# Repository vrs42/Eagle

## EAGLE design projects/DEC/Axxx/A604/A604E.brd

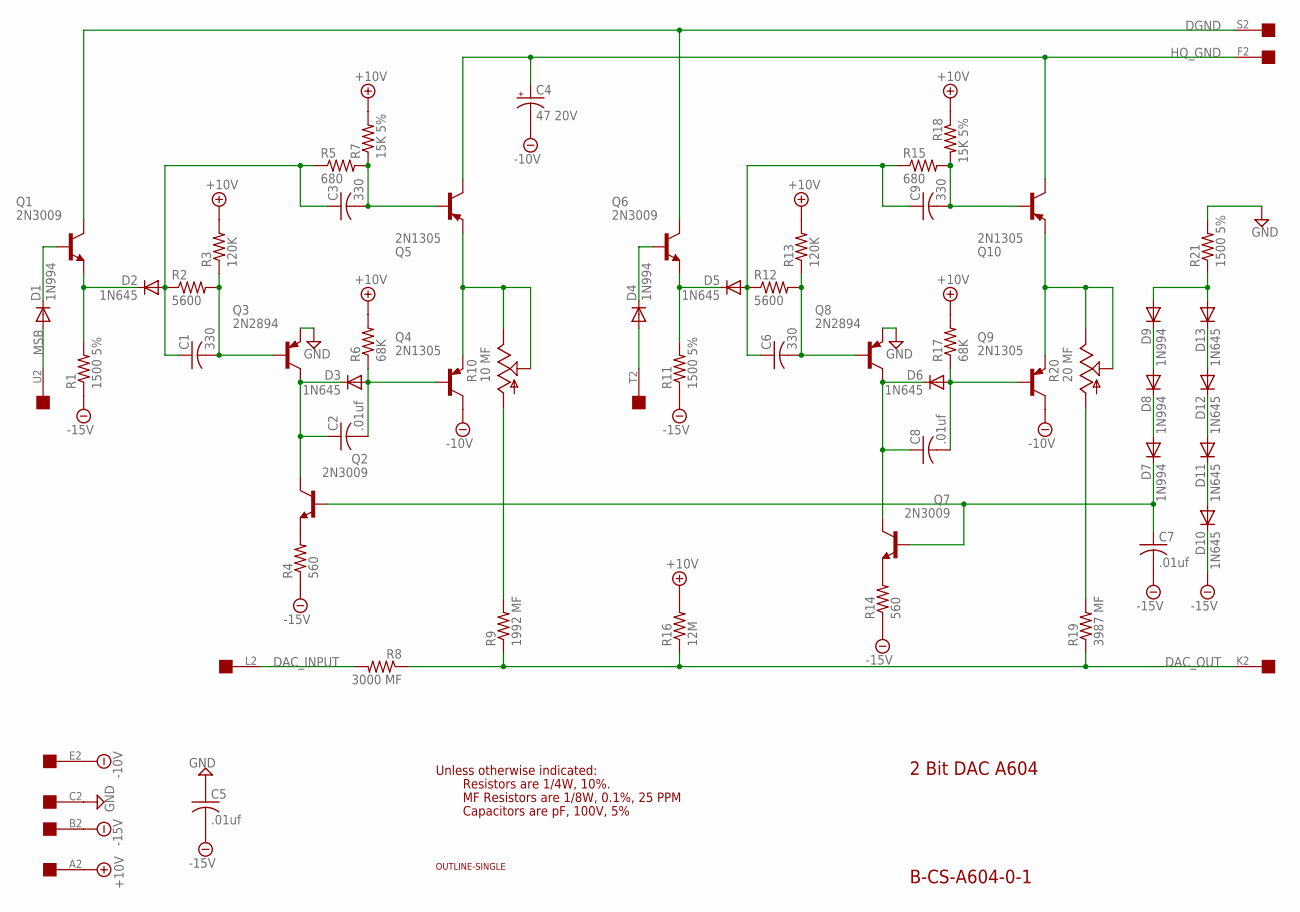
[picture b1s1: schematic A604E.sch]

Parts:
C1, C3, C6, C9: 330; C075-032X103
C2, C5, C7, C8: .01uf; C050-025X075
C4: 47 20V; E22-6
D1, D4, D7, D8, D9: 1N994; DO35-10
D2, D3, D5, D6, D10, D11, D12, D13: 1N645; DO35-10
Q1, Q2, Q6, Q7: 2N3009; TO39
Q3, Q8: 2N2894; TO39
Q4, Q5, Q9, Q10: 2N1305; TO39
R1, R11, R21: 1500 5%; 0207/10
R2, R12: 5600; 0207/10
R3, R13: 120K; 0207/10
R4, R14: 560; 0207/10
R5, R15: 680; 0207/10
R6, R17: 68K; 0207/10
R7, R18: 15K 5%; 0207/10
R8: 3000 MF; 0309/12
R9: 1992 MF; 0309/12
R10: 10 MF; S75P
R16: 12M; 0207/10
R19: 3987 MF; 0309/12
R20: 20 MF; S75P
U$1: OUTLINE-SINGLE; SINGLE
U$3: EDGE-1; EDGE-CON1

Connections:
+10V: R3.2, R6.2, R7.2, R13.2, R16.2, R17.2, R18.1, U$3.A2
-10V: C4.-, Q4.3 (C), Q9.3 (C), U$3.E2
-15V: C5.2, C7.2, D10.C, R1.1, R4.1, R11.1, R14.1, U$3.B2
DAC_INPUT: R8.2, U$3.L2
DAC_OUT: R8.1, R9.1, R16.1, R19.1, U$3.K2
DGND: Q1.3 (C), Q6.3 (C), U$3.S2
GND: C5.1, Q3.1 (E), Q8.1 (E), R21.2, U$3.C2
HQ_GND: C4.+, Q5.3 (C), Q10.3 (C), U$3.F2
MSB: D1.A, U$3.U2
unnamed: D1.C, Q1.2 (B)
unnamed: D2.C, Q1.1 (E), R1.2
unnamed: C1.1, C3.1, D2.A, R2.1, R5.1
unnamed: C1.2, Q3.2 (B), R2.2, R3.1
unnamed: C3.2, Q5.2 (B), R5.2, R7.1
unnamed: C2.1, D3.C, Q2.3 (C), Q3.3 (C)
unnamed: C2.2, D3.A, Q4.2 (B), R6.1
unnamed: Q4.1 (E), Q5.1 (E), R10.E, R10.S
unnamed: D4.C, Q6.2 (B)
unnamed: D5.C, Q6.1 (E), R11.2
unnamed: C6.1, C9.1, D5.A, R12.1, R15.1
unnamed: C6.2, Q8.2 (B), R12.2, R13.1
unnamed: C9.2, Q10.2 (B), R15.2, R18.2
unnamed: C8.1, D6.C, Q7.3 (C), Q8.3 (C)
unnamed: C8.2, D6.A, Q9.2 (B), R17.1
unnamed: Q9.1 (E), Q10.1 (E), R20.E, R20.S
unnamed: Q2.1 (E), R4.2
unnamed: R9.2, R10.A
unnamed: R19.2, R20.A
unnamed: Q7.1 (E), R14.2
unnamed: C7.1, D7.C, Q2.2 (B), Q7.2 (B)
unnamed: D8.A, D9.C
unnamed: D7.A, D8.C
unnamed: D10.A, D11.C
unnamed: D12.A, D13.C
unnamed: D11.A, D12.C
unnamed: D9.A, D13.A, R21.1
T2: D4.A, U$3.T2

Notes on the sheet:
2 Bit DAC A604
B-CS-A604-0-1
Unless otherwise indicated:
Resistors are 1/4W, 10%.
MF Resistors are 1/8W, 0.1%, 25 PPM
Capacitors are pF, 100V, 5%

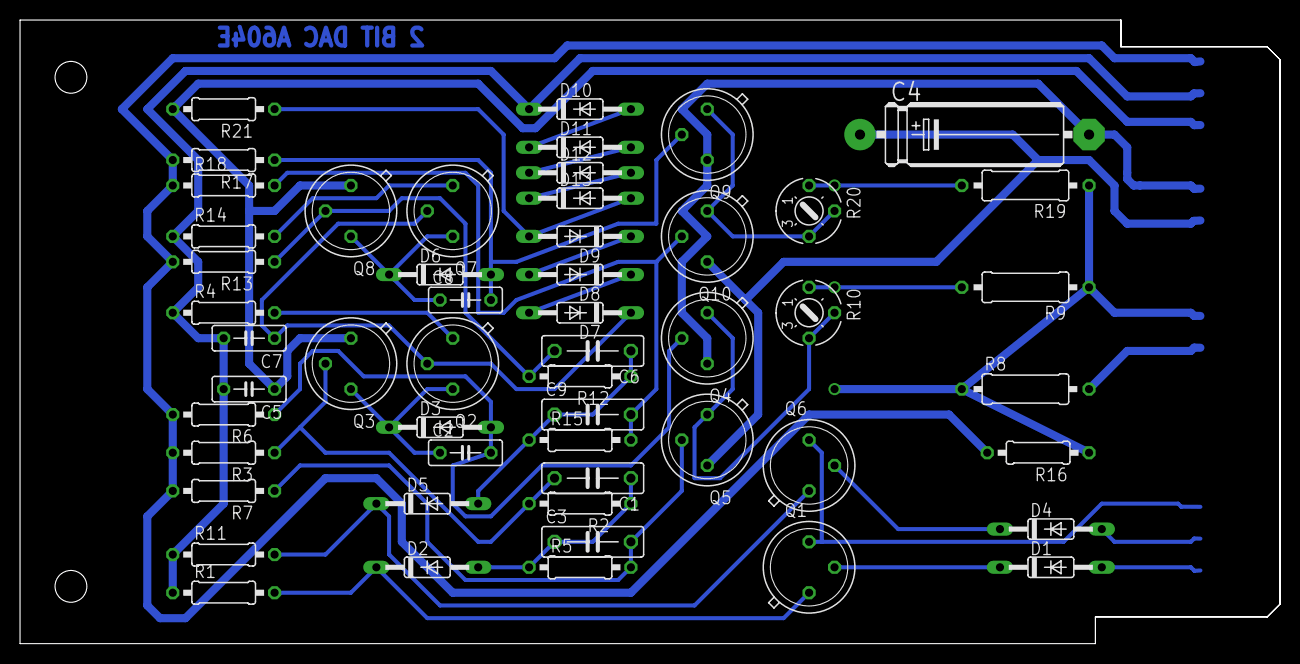
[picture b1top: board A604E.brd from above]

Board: 2 copper layers, 125.7 x 62.2 mm, 55 parts (0 on the bottom side), 37 nets.

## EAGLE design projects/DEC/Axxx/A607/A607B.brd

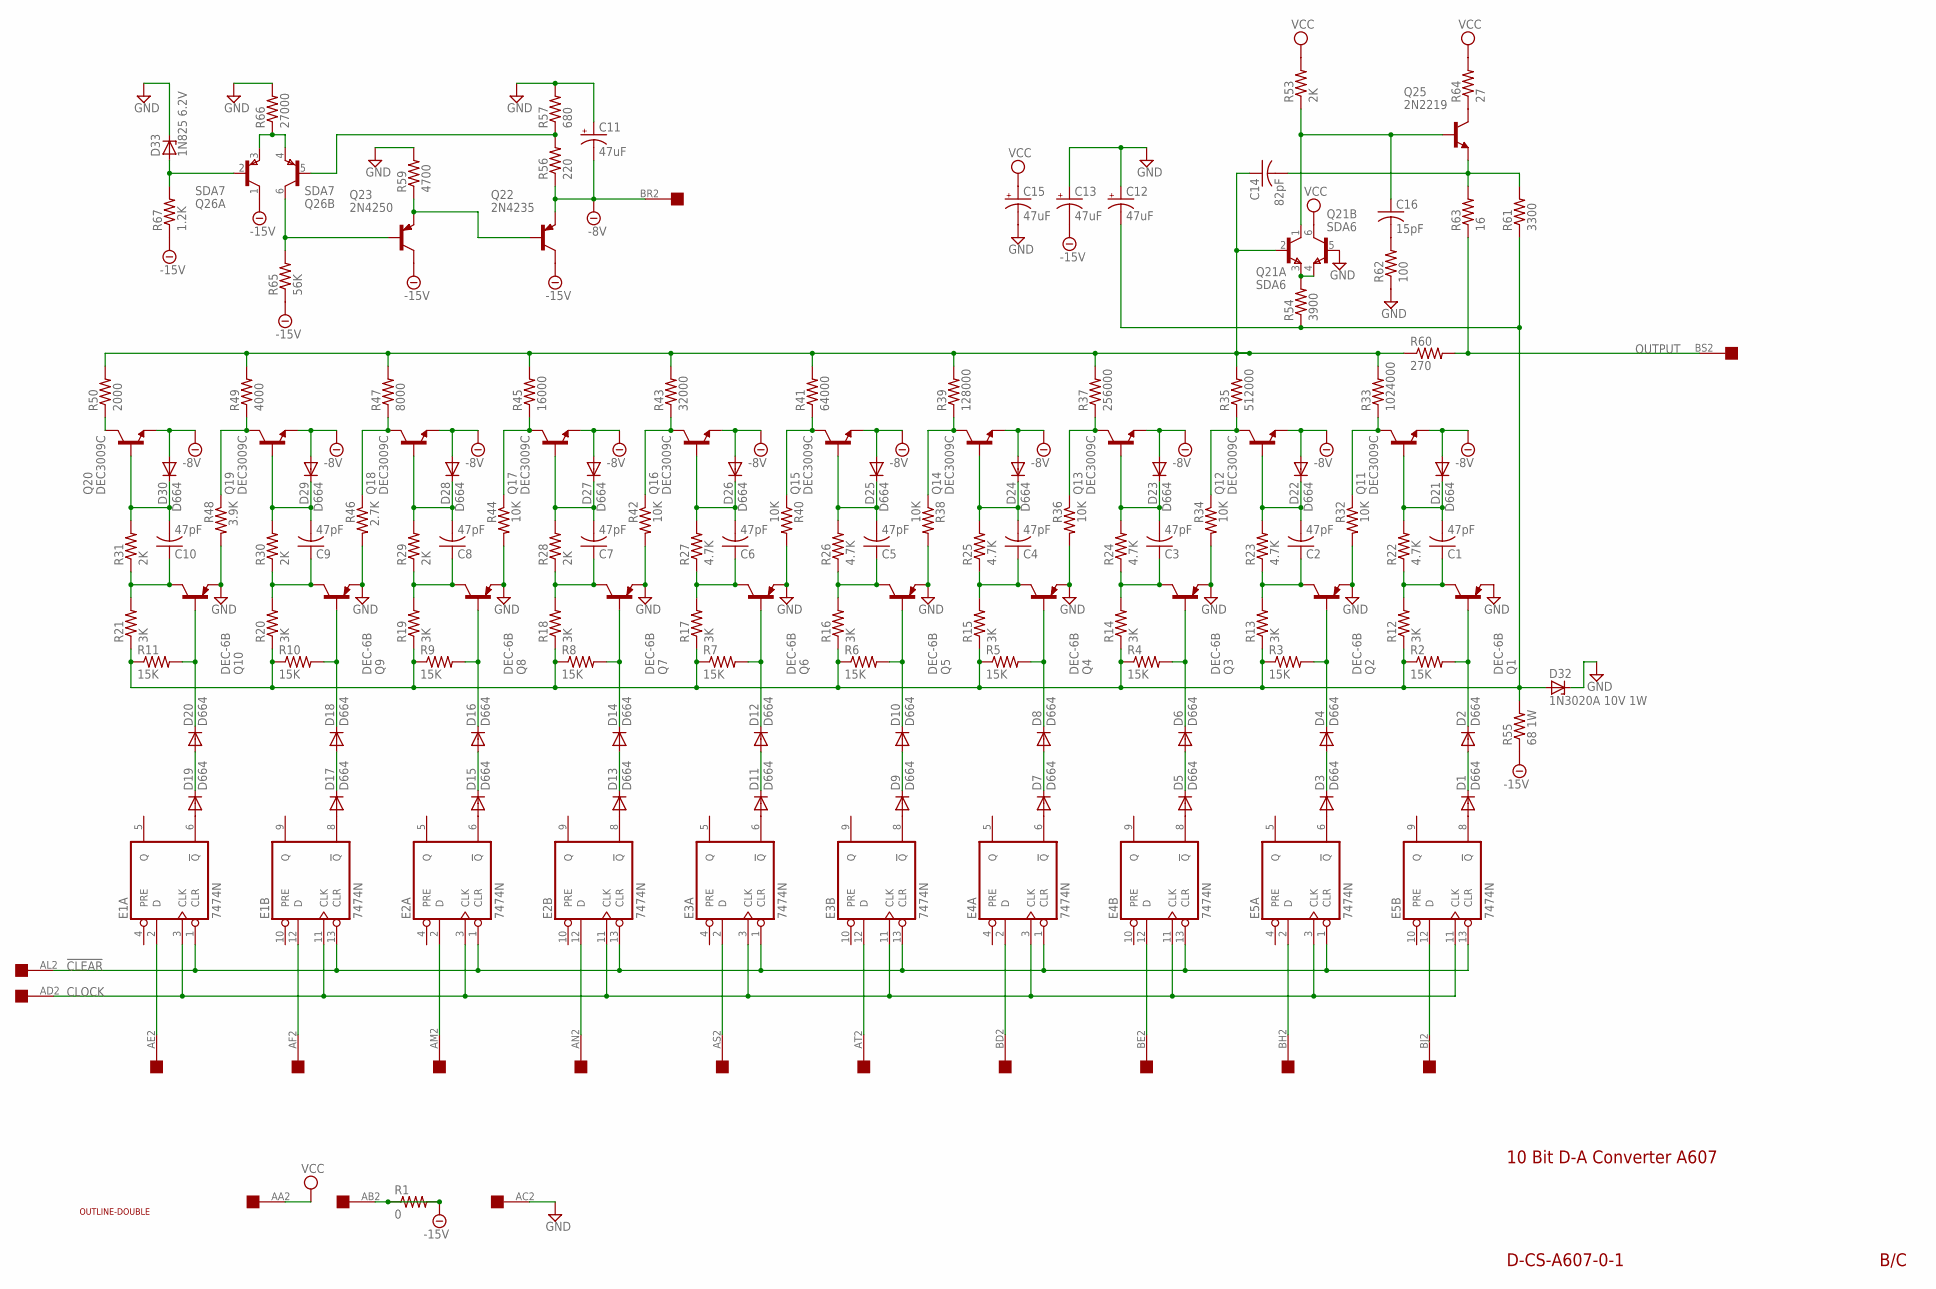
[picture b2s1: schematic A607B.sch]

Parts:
C1, C2, C3, C4, C5, C6, C7, C8, C9, C10: 47pF; C075-032X103
C11, C12, C13, C15: 47uF; E25-9
C14: 82pF; C050-025X075
C16: 15pF; C050-025X075
D1, D2, D3, D4, D5, D6, D7, D8, D9, D10, D11, D12, D13, D14, D15, D16, D17, D18, D19, D20, D21, D22, D23, D24, D25, D26, D27, D28, D29, D30: D664; DO35-10
D32: 1N3020A 10V 1W; DO13M
D33: 1N825 6.2V; DO35Z10
E1, E2, E3, E4, E5: 7474N; DIL14
Q1, Q2, Q3, Q4, Q5, Q6, Q7, Q8, Q9, Q10: DEC-6B; TO5
Q11, Q12, Q13, Q14, Q15, Q16, Q17, Q18, Q19, Q20: DEC3009C; TO5
Q21: SDA6; TO78
Q22: 2N4235; TO5
Q23: 2N4250; TO5
Q25: 2N2219; TO5
Q26: SDA7; TO78
R1: 0; 0818/25
R2, R3, R4, R5, R6, R7, R8, R9, R10, R11: 15K; 0207/10
R12, R13, R14, R15, R16, R17, R18, R19, R20, R21: 3K; 0207/10
R22, R23, R24, R25, R26, R27: 4.7K; 0207/10
R28, R29, R30, R31, R53: 2K; 0207/10
R32, R34, R36, R38, R40, R42, R44: 10K; 0207/10
R33: 1024000; 0414/20
R35: 512000; 0414/20
R37: 256000; 0207/15
R39: 128000; 0207/15
R41: 64000; 0207/15
R43: 32000; 0207/15
R45: 16000; 0207/15
R46: 2.7K; 0207/10
R47: 8000; 0207/15
R48: 3.9K; 0207/10
R49: 4000; 0207/15
R50: 2000; 0207/15
R54: 3900; 0207/10
R55: 68 1W; 0818/25
R56: 220; 0207/10
R57: 680; 0207/10
R59: 4700; 0207/10
R60: 270; 0207/10
R61: 3300; 0207/10
R62: 100; 0207/10
R63: 16; 0207/10
R64: 27; 0207/10
R65: 56K; 0207/10
R66: 27000; 0207/10
R67: 1.2K; 0207/10
U$1: OUTLINE-DOUBLE; DOUBLE
U$2: DOUBLE; EDGE-CON4

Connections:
!CLEAR: E1.1 (CLR), E1.13 (CLR), E2.1 (CLR), E2.13 (CLR), E3.1 (CLR), E3.13 (CLR), E4.1 (CLR), E4.13 (CLR), E5.1 (CLR), E5.13 (CLR), U$2.AL2
-8V: C11.-, D21.A, D22.A, D23.A, D24.A, D25.A, D26.A, D27.A, D28.A, D29.A, D30.A, Q11.1 (E), Q12.1 (E), Q13.1 (E), Q14.1 (E), Q15.1 (E), Q16.1 (E), Q17.1 (E), Q18.1 (E), Q19.1 (E), Q20.1 (E), Q22.1 (E), R56.1, U$2.BR2
-15V: C13.-, Q22.3 (C), Q23.3 (C), Q26.1 (C), R1.1, R1.2, R55.1, R65.1, R67.1, U$2.AB2
CLOCK: E1.3 (CLK), E1.11 (CLK), E2.3 (CLK), E2.11 (CLK), E3.3 (CLK), E3.11 (CLK), E4.3 (CLK), E4.11 (CLK), E5.3 (CLK), E5.11 (CLK), U$2.AD2
GND: C11.+, C12.+, C13.+, C15.-, D32.C, D33.C, E1.7 (GND), E2.7 (GND), E3.7 (GND), E4.7 (GND), E5.7 (GND), Q1.1 (E), Q2.1 (E), Q3.1 (E), Q4.1 (E), Q5.1 (E), Q6.1 (E), Q7.1 (E), Q8.1 (E), Q9.1 (E), Q10.1 (E), Q21.5 (B), R32.2, R34.2, R36.2, R38.2, R40.2, R42.2, R44.2, R46.2, R48.2, R57.2, R59.2, R62.1, R66.2, U$2.AC2
unnamed: E1.2 (D), U$2.AE2
unnamed: E1.12 (D), U$2.AF2
unnamed: E2.2 (D), U$2.AM2
unnamed: E2.12 (D), U$2.AN2
unnamed: E3.2 (D), U$2.AS2
unnamed: E3.12 (D), U$2.AT2
unnamed: E4.2 (D), U$2.BD2
unnamed: E4.12 (D), U$2.BE2
unnamed: E5.2 (D), U$2.BH2
unnamed: E5.12 (D), U$2.BJ2
unnamed: D1.A, E5.8 (!Q)
unnamed: D3.A, E5.6 (!Q)
unnamed: D5.A, E4.8 (!Q)
unnamed: D7.A, E4.6 (!Q)
unnamed: D9.A, E3.8 (!Q)
unnamed: D11.A, E3.6 (!Q)
unnamed: D13.A, E2.8 (!Q)
unnamed: D15.A, E2.6 (!Q)
unnamed: D17.A, E1.8 (!Q)
unnamed: D19.A, E1.6 (!Q)
unnamed: D19.C, D20.A
unnamed: D17.C, D18.A
unnamed: D15.C, D16.A
unnamed: D13.C, D14.A
unnamed: D11.C, D12.A
unnamed: D9.C, D10.A
unnamed: D7.C, D8.A
unnamed: D5.C, D6.A
unnamed: D3.C, D4.A
unnamed: D1.C, D2.A
unnamed: D20.C, Q10.2 (B), R11.2
unnamed: D18.C, Q9.2 (B), R10.2
unnamed: D16.C, Q8.2 (B), R9.2
unnamed: D14.C, Q7.2 (B), R8.2
unnamed: D12.C, Q6.2 (B), R7.2
unnamed: D10.C, Q5.2 (B), R6.2
unnamed: D8.C, Q4.2 (B), R5.2
unnamed: D6.C, Q3.2 (B), R4.2
unnamed: D4.C, Q2.2 (B), R3.2
unnamed: D2.C, Q1.2 (B), R2.2
unnamed: C12.-, D32.A, R2.1, R3.1, R4.1, R5.1, R6.1, R7.1, R8.1, R9.1, R10.1, R11.1, R12.1, R13.1, R14.1, R15.1, R16.1, R17.1, R18.1, R19.1, R20.1, R21.1, R54.1, R55.2, R61.1
unnamed: Q23.2 (B), Q26.6 (C), R65.2
unnamed: Q26.3 (E), Q26.4 (E), R66.1
unnamed: Q22.2 (B), Q23.1 (E), R59.1
unnamed: Q26.5 (B), R56.2, R57.1
unnamed: D33.A, Q26.2 (B), R67.2
unnamed: C1.1, Q1.3 (C), R12.2, R22.1
unnamed: C2.1, Q2.3 (C), R13.2, R23.1
unnamed: C3.1, Q3.3 (C), R14.2, R24.1
unnamed: C4.1, Q4.3 (C), R15.2, R25.1
unnamed: C6.1, Q6.3 (C), R17.2, R27.1
unnamed: C7.1, Q7.3 (C), R18.2, R28.1
unnamed: C8.1, Q8.3 (C), R19.2, R29.1
unnamed: C9.1, Q9.3 (C), R20.2, R30.1
unnamed: C10.1, Q10.3 (C), R21.2, R31.1
unnamed: C5.1, Q5.3 (C), R16.2, R26.1
unnamed: C9.2, D29.C, Q19.2 (B), R30.2
unnamed: C1.2, D21.C, Q11.2 (B), R22.2
unnamed: C2.2, D22.C, Q12.2 (B), R23.2
unnamed: C3.2, D23.C, Q13.2 (B), R24.2
unnamed: C4.2, D24.C, Q14.2 (B), R25.2
unnamed: C5.2, D25.C, Q15.2 (B), R26.2
unnamed: C6.2, D26.C, Q16.2 (B), R27.2
unnamed: C7.2, D27.C, Q17.2 (B), R28.2
unnamed: C8.2, D28.C, Q18.2 (B), R29.2
unnamed: C10.2, D30.C, Q20.2 (B), R31.2
unnamed: Q20.3 (C), R50.1
unnamed: Q19.3 (C), R48.1, R49.1
unnamed: Q18.3 (C), R46.1, R47.1
unnamed: Q17.3 (C), R44.1, R45.1
unnamed: Q11.3 (C), R32.1, R33.1
unnamed: Q12.3 (C), R34.1, R35.1
unnamed: Q13.3 (C), R36.1, R37.1
unnamed: Q14.3 (C), R38.1, R39.1
unnamed: Q15.3 (C), R40.1, R41.1
unnamed: Q16.3 (C), R42.1, R43.1
unnamed: Q25.3 (C), R64.1
unnamed: C16.1, Q21.1 (C), Q25.2 (B), R53.1
unnamed: C14.1, Q21.2 (B), R33.2, R35.2, R37.2, R39.2, R41.2, R43.2, R45.2, R47.2, R49.2, R50.2, R60.1
unnamed: C14.2, Q25.1 (E), R61.2, R63.2
unnamed: Q21.3 (E), Q21.4 (E), R54.2
unnamed: C16.2, R62.2
OUTPUT: R60.2, R63.1, U$2.BS2
VCC: C15.+, E1.14 (VCC), E2.14 (VCC), E3.14 (VCC), E4.14 (VCC), E5.14 (VCC), Q21.6 (C), R53.2, R64.2, U$2.AA2

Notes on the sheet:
B/C
10 Bit D-A Converter A607
D-CS-A607-0-1

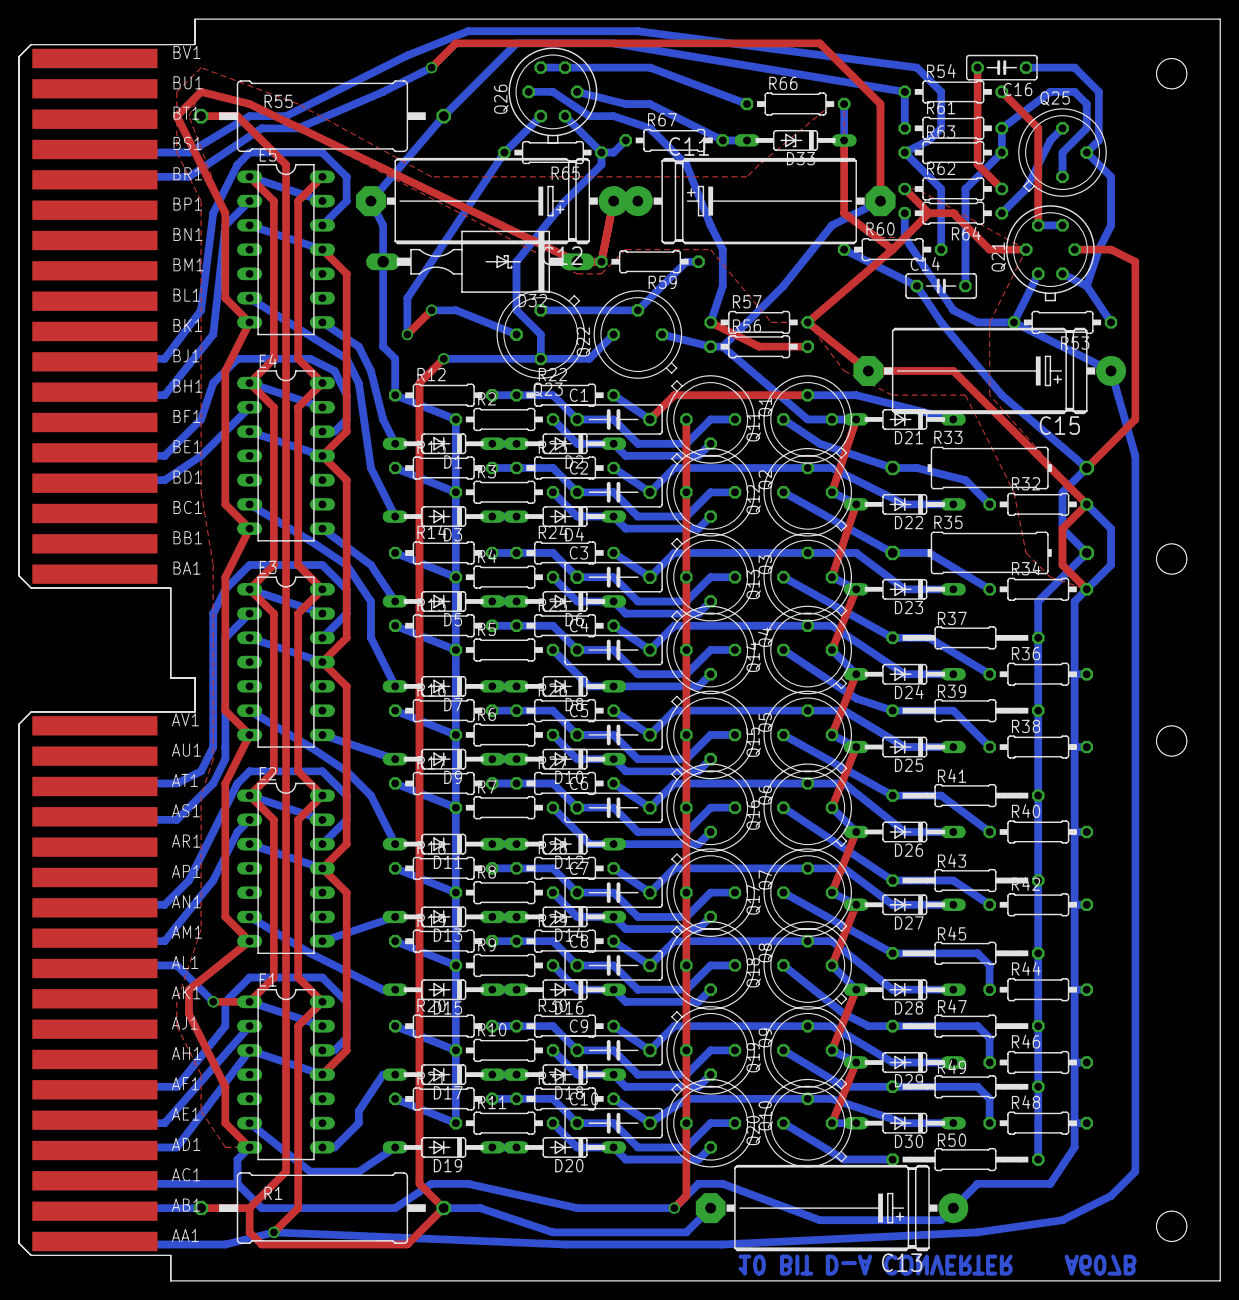
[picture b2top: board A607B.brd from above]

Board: 3 copper layers, 125.7 x 132.1 mm, 144 parts (0 on the bottom side), 89 nets.

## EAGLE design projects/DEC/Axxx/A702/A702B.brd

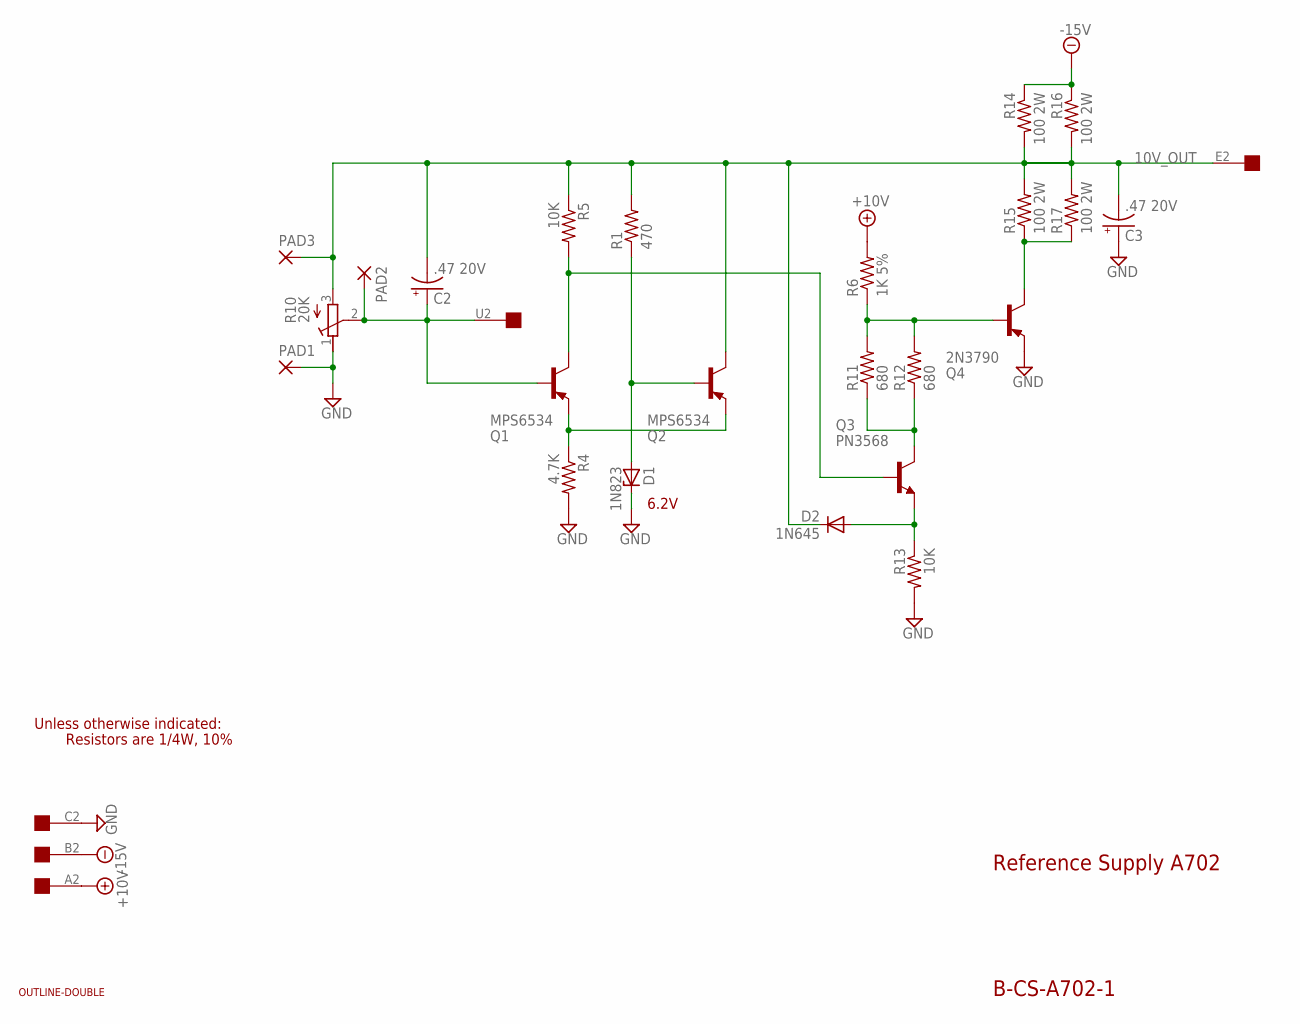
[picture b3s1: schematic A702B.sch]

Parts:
C2, C3: .47 20V; E22-6
D1: 1N823; DO35Z10
D2: 1N645; DO35-10
PAD1, PAD2, PAD3: 2,54/0,8
Q1, Q2: MPS6534; TO39
Q3: PN3568; TO5
Q4: 2N3790; TO3
R1: 470; 0207/10
R4: 4.7K; 0207/10
R5, R13: 10K; 0207/10
R6: 1K 5%; 0207/10
R10: 20K; 3006Y
R11, R12: 680; 0207/10
R14, R15, R16, R17: 100 2W; P0817/22
U$1: OUTLINE-DOUBLE; DOUBLE
U$3: EDGE-1; EDGE-CON1

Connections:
10V_OUT: C2.-, C3.-, D2.C, PAD3.1, Q2.3 (C), R1.2, R5.1, R10.3 (E), R14.2, R15.2, R16.2, R17.2, U$3.E2
+10V: R6.2, U$3.A2
-15V: R14.1, R16.1, U$3.B2
GND: C3.+, D1.C, PAD1.1, Q4.E, R4.2, R10.1 (A), R13.2, U$3.C2
unnamed: Q1.1 (E), Q2.1 (E), R4.1
unnamed: Q3.3 (C), R11.1, R12.1
unnamed: Q1.3 (C), Q3.2 (B), R5.2
unnamed: Q4.C, R15.1, R17.1
unnamed: D2.A, Q3.1 (E), R13.1
unnamed: D1.A, Q2.2 (B), R1.1
unnamed: Q4.B, R6.1, R11.2, R12.2
U2: C2.+, PAD2.1, Q1.2 (B), R10.2 (S), U$3.U2

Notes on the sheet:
Reference Supply A702
B-CS-A702-1
Unless otherwise indicated:
Resistors are 1/4W, 10%
6.2V

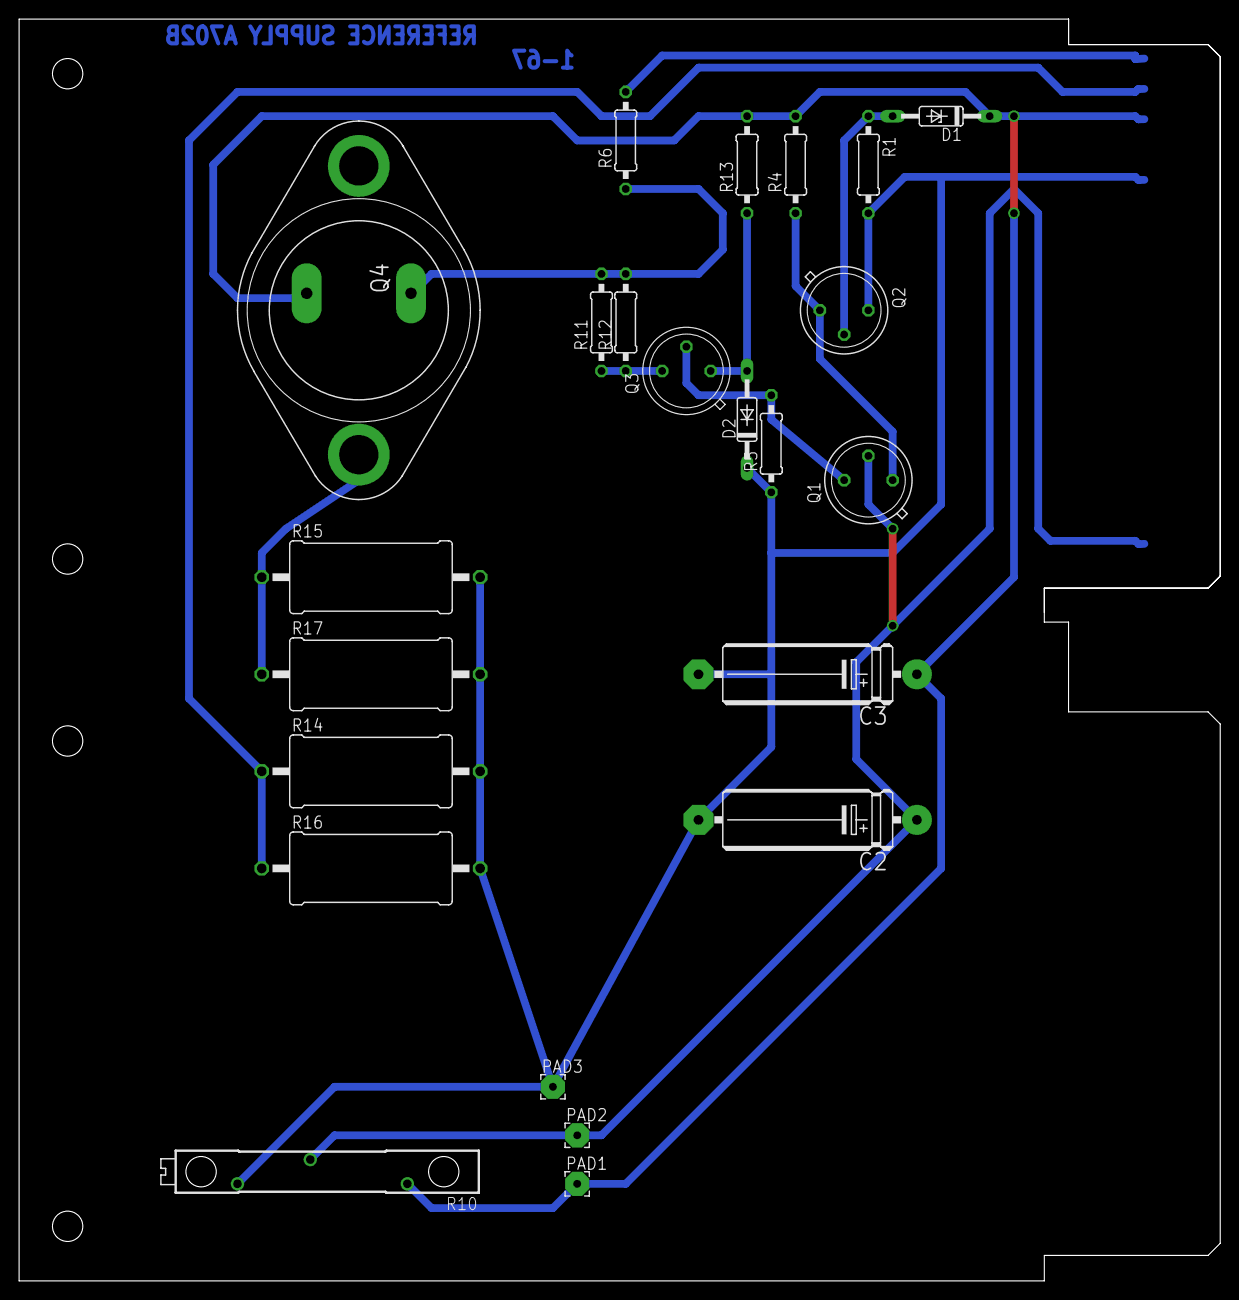
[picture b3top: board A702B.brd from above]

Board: 2 copper layers, 125.7 x 132.1 mm, 25 parts (0 on the bottom side), 12 nets.
